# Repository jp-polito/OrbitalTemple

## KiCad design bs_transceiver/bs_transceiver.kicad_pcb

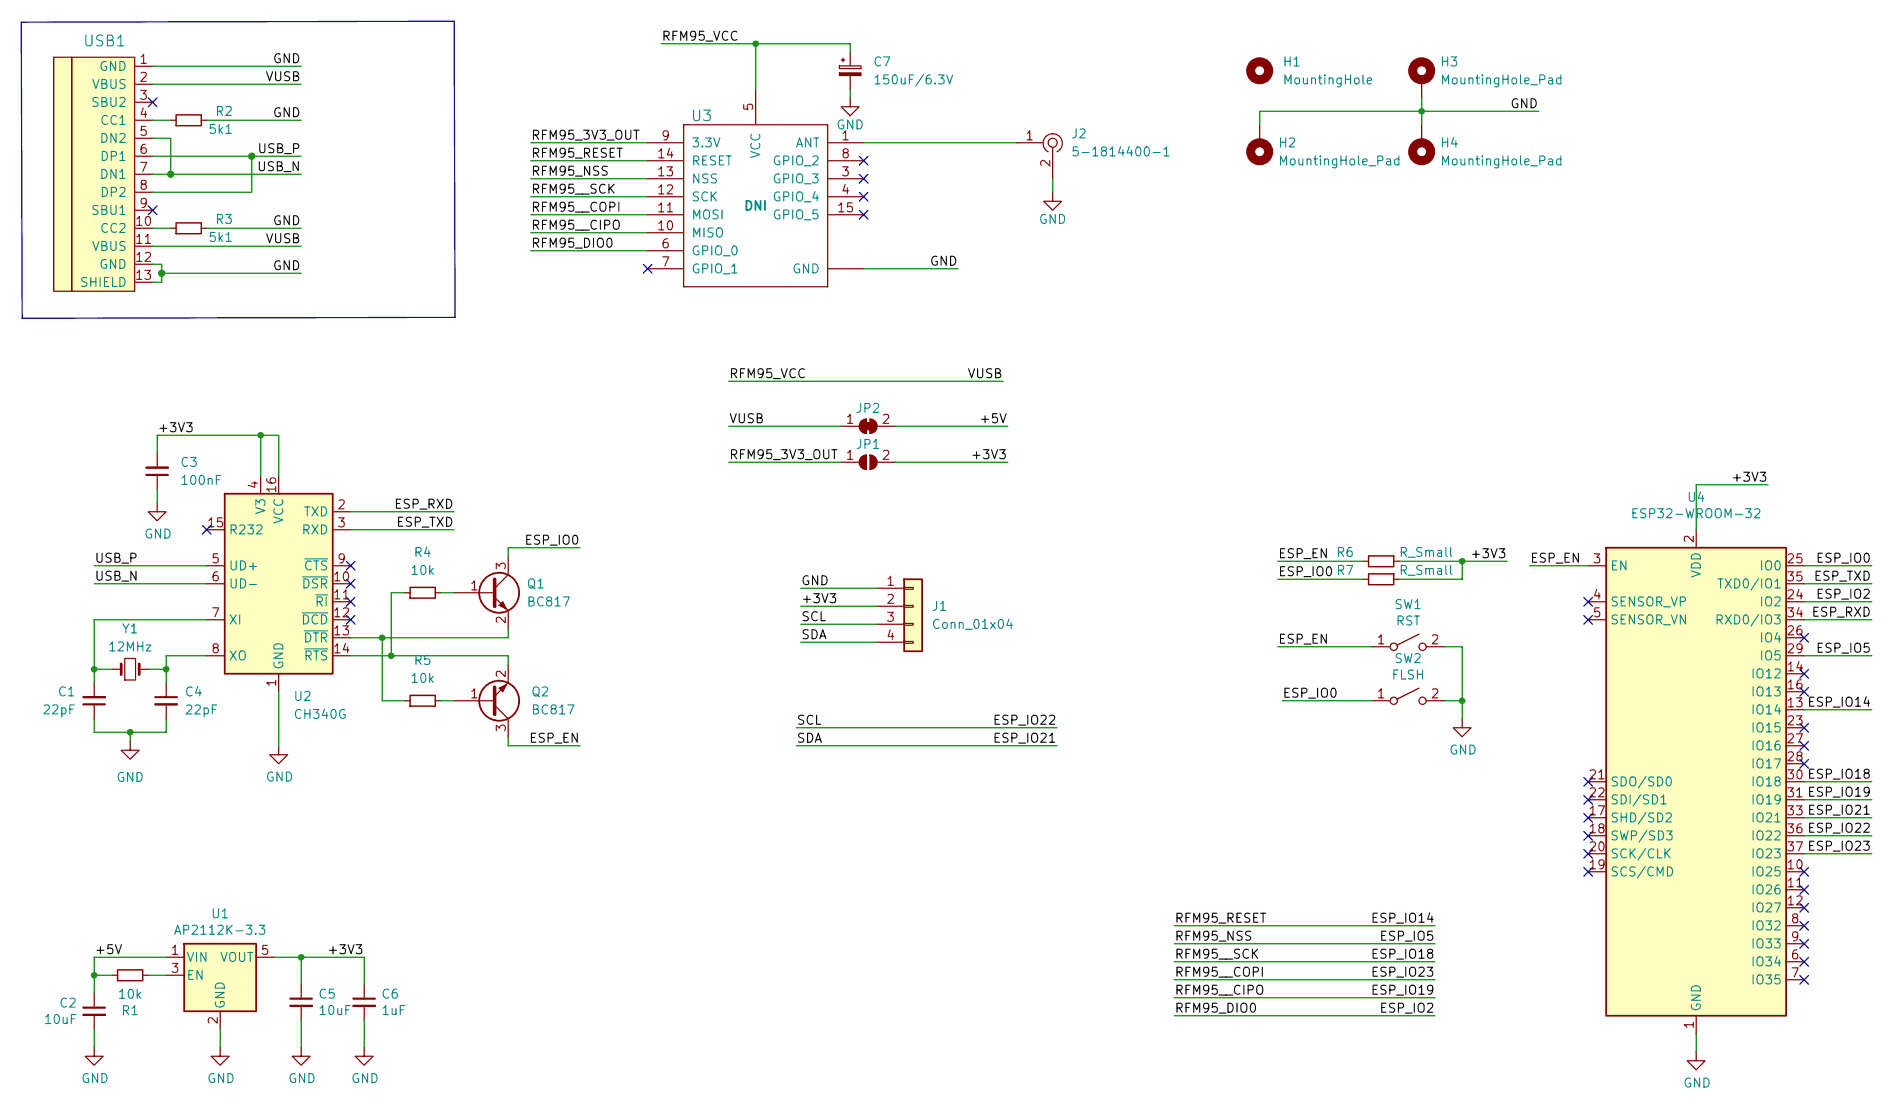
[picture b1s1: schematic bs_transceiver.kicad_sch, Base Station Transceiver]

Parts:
C1, C4: 22pF; C_0603_1608Metric
C2, C5: 10uF; C_0603_1608Metric
C3: 100nF; C_0603_1608Metric
C6: 1uF; C_0603_1608Metric
C7: 150uF/6.3V; CP_EIA-7343-15_Kemet-W; Mouser Part 80-T520V157M006E025
H1: MountingHole; MountingHole_3.2mm_M3
H2, H3, H4: MountingHole_Pad; MountingHole_3.2mm_M3_DIN965_Pad_TopOnly
J1: Conn_01x04; PinHeader_1x04_P2.54mm_Vertical
J2: 5-1814400-1; RF_SMA_RightAngle_5-1814400-1; MPN 5-1814400-1; Digi-Key_PN A97593-ND
JP1: SolderJumper_2_Open; SolderJumper-2_P1.3mm_Open_RoundedPad1.0x1.5mm
JP2: SolderJumper_2_Bridged; SolderJumper-2_P1.3mm_Bridged_RoundedPad1.0x1.5mm
Q1, Q2: BC817; SOT-23
R1, R4, R5: 10k; R_0603_1608Metric
R2, R3: 5k1; R_0603_1608Metric
R6, R7: R_Small; R_0603_1608Metric
SW1: RST; SW_SPST_FSMSM
SW2: FLSH; SW_SPST_FSMSM
U1: AP2112K-3.3; SOT-23-5
U2: CH340G; SOIC-16_3.9x9.9mm_P1.27mm
U3: RFM98PW; RFM95PW
U4: ESP32-WROOM-32
USB1: HRO-TYPE-C-31-M-12; HRO-TYPE-C-31-M-12-HandSoldering
Y1: 12MHz; Crystal_SMD_HC49-SD

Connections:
/+3V3: C3.2, C5.1, C6.1, J1.2, JP1.2 (B), R6.1, R7.1, U1.5 (VOUT), U2.4 (V3), U2.16 (VCC), U4.2 (VDD)
/+5V: C2.1, JP2.2 (B), R1.1, U1.1 (VIN)
/ESP_EN: Q2.3 (C), R6.2, SW1.1 (A), U4.3 (EN)
/ESP_IO0: Q1.3 (C), R7.2, SW2.1 (A), U4.25 (IO0)
/ESP_IO2: U3.6 (GPIO_0), U4.24 (IO2)
/ESP_IO5: U3.13 (NSS), U4.29 (IO5)
/ESP_IO14: U3.14 (RESET), U4.13 (IO14)
/ESP_IO18: U3.12 (SCK), U4.30 (IO18)
/ESP_IO19: U3.10 (MISO), U4.31 (IO19)
/ESP_IO21: J1.4, U4.33 (IO21)
/ESP_IO22: J1.3, U4.36 (IO22)
/ESP_IO23: U3.11 (MOSI), U4.37 (IO23)
/ESP_RXD: U2.2 (TXD), U4.34 (RXD0/IO3)
/ESP_TXD: U2.3 (RXD), U4.35 (TXD0/IO1)
/RFM95_3V3_OUT: JP1.1 (A), U3.9 (3.3V)
/RFM95_VCC: C7.1, JP2.1 (A), U3.5 (VCC), USB1.2 (VBUS), USB1.11 (VBUS)
/USB_N: U2.6 (UD-), USB1.5 (DN2), USB1.7 (DN1)
/USB_P: U2.5 (UD+), USB1.6 (DP1), USB1.8 (DP2)
GND: C1.1, C2.2, C3.1, C4.2, C5.2, C6.2, C7.2, H2.1, H3.1, H4.1, J1.1, J2.2, R2.2, R3.2, SW1.2 (B), SW2.2 (B), U1.2 (GND), U2.1 (GND), U3.2 (GND), U3.16 (GND), U3.17 (GND), U4.1 (GND), U4.15 (GND), U4.38 (GND), U4.39 (GND), USB1.1 (GND), USB1.12 (GND), USB1.13 (SHIELD)
unnamed: C1.2, U2.7 (XI), Y1.1
unnamed: C4.1, U2.8 (XO), Y1.2
unnamed: J2.1, U3.1 (ANT)
unnamed: Q1.1 (B), R4.2
unnamed: Q1.2 (E), R5.1, U2.13 (~DTR)
unnamed: Q2.1 (B), R5.2
unnamed: Q2.2 (E), R4.1, U2.14 (~RTS)
unnamed: R1.2, U1.3 (EN)
unnamed: R2.1, USB1.4 (CC1)
unnamed: R3.1, USB1.10 (CC2)

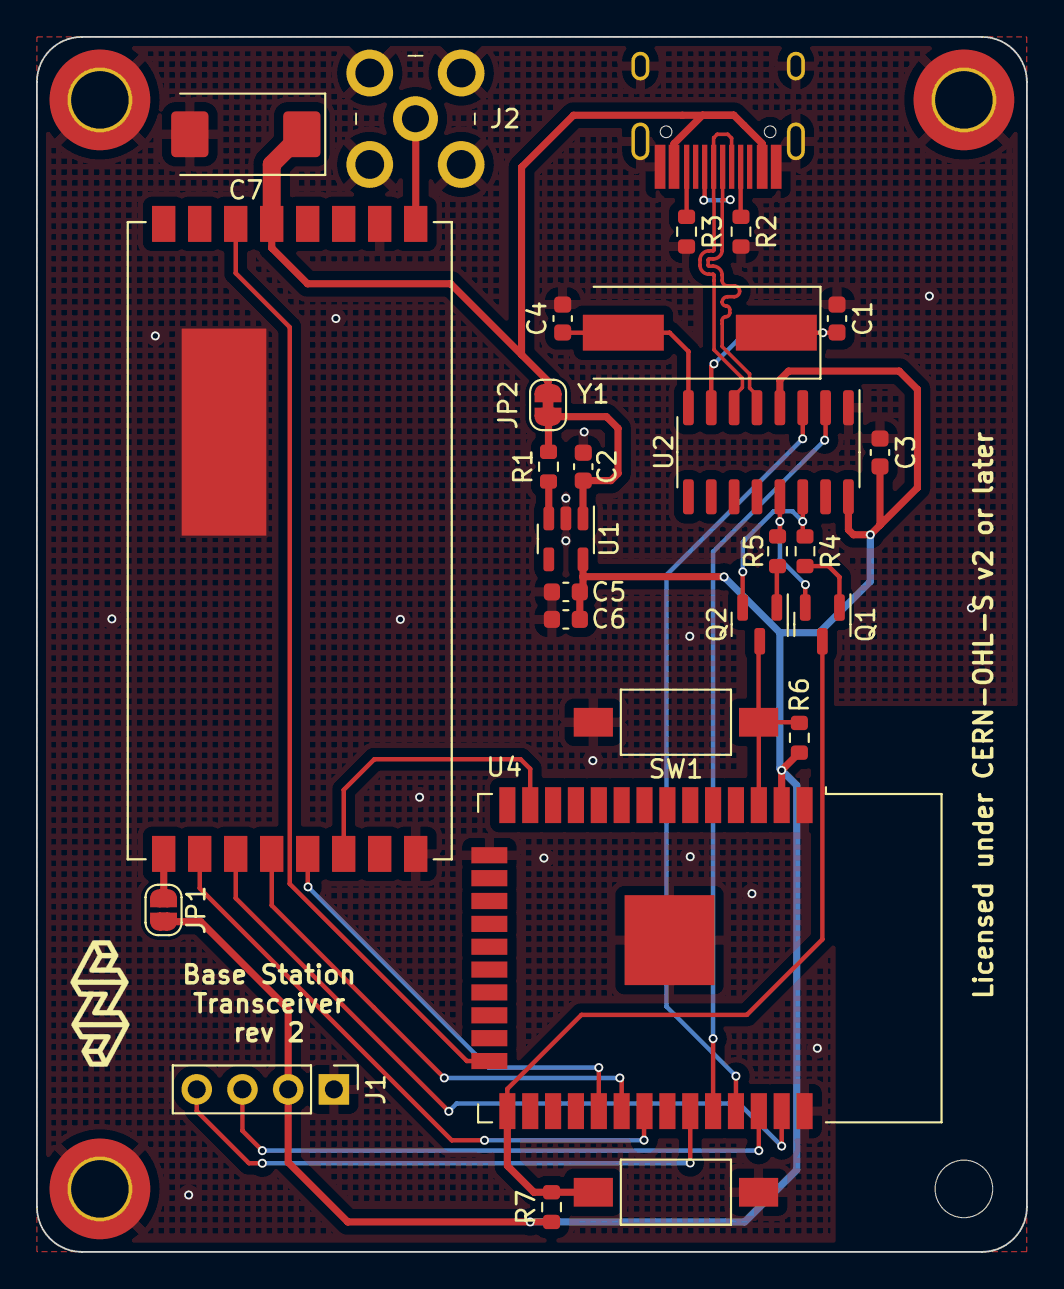
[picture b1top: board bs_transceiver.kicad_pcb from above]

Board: 2 copper layers, 55.0 x 67.5 mm, 32 parts (0 on the bottom side), 29 nets.

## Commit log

2023-04-26 Create Hardware

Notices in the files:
bs_transceiver/bs_transceiver.kicad_pcb:
Licensed under CERN-OHL-S v2 or later
